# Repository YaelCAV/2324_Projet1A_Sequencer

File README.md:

# Projet-Sequenceur
> On souhaite créer un séquenceur musical qui émet des notes sur demande de l'utilisateur. Les notes doivent être variées et configurables, par exemple on souhaite pouvoir modifier leur hauteur, le nombre de répétitions par minute (bpm), et combiner les notes.
Pour cela on utilise sur conseil de l'un de nos professeurs un générateur de son programmable de Comodore 64 (dénomée MOS 6581) sortie en 1982.
La documentation de cette puce est facile d'accès et les possibilités qu'elle offrent satisfont nos exigences.
Comme mode de récupération du signal de sortie nous avons finalement choisi de proposer une sortie MIDI et Jack, il n'y a pas de haut-parleur intégré à notre séquenceur. L'alimentation de notre machine se fera par ailleurs via un port USB-C.

# Equipe
* Yael CAVAILLE-VOISIN
* Alexis NAUD
* Benoit LOMBARD
* Guilhem BOULARAN
* Louis GEORGE
> Rajouter vos github, linked in, etc...

# Journal de bord
> Déroulé séance par séance

## Séance 1 création du git, rédaction du cahier des charges et du plan, révision du cahier des charges.
## Séance 2 rendu du diagramme d'architecture, et des 3 bons de commande de composants, révision du cahier des charges et recherche des composants.
## Séance 3 CAO avec Kicad, changement de composants (boutons et LEDs RGB, hauts-parleurs, ampli audio).
## Séance 4 fin de conception du PCB et routage complet.
## Séance 5 récupération des composants et soudure, conception 3D, Architecture du code
## Séance 6 soudure + résolution des problèmes (d'empreinte des boutons-LED RG au lieu de RB via des PCB-adaptateurs imprimés à l'ENSEA), conception 3D
## Séance 7 soudure + résolution de problèmes, code, conception 3D
## Séance 8 soudure + résolution de problèmes, code, conception 3D
## Séance 9 code, présentation en séance, màj des livrables, résolution de problèmes liés au PCB et au processeur !
## Séance 10 code, création, compilation et vérification des livrables.

# Livrables
## PCB
> Présentation du schéma (grandes lignes) + PCB

## Code
> Architecture de votre code

## Rendu final
> Video ici de votre projet

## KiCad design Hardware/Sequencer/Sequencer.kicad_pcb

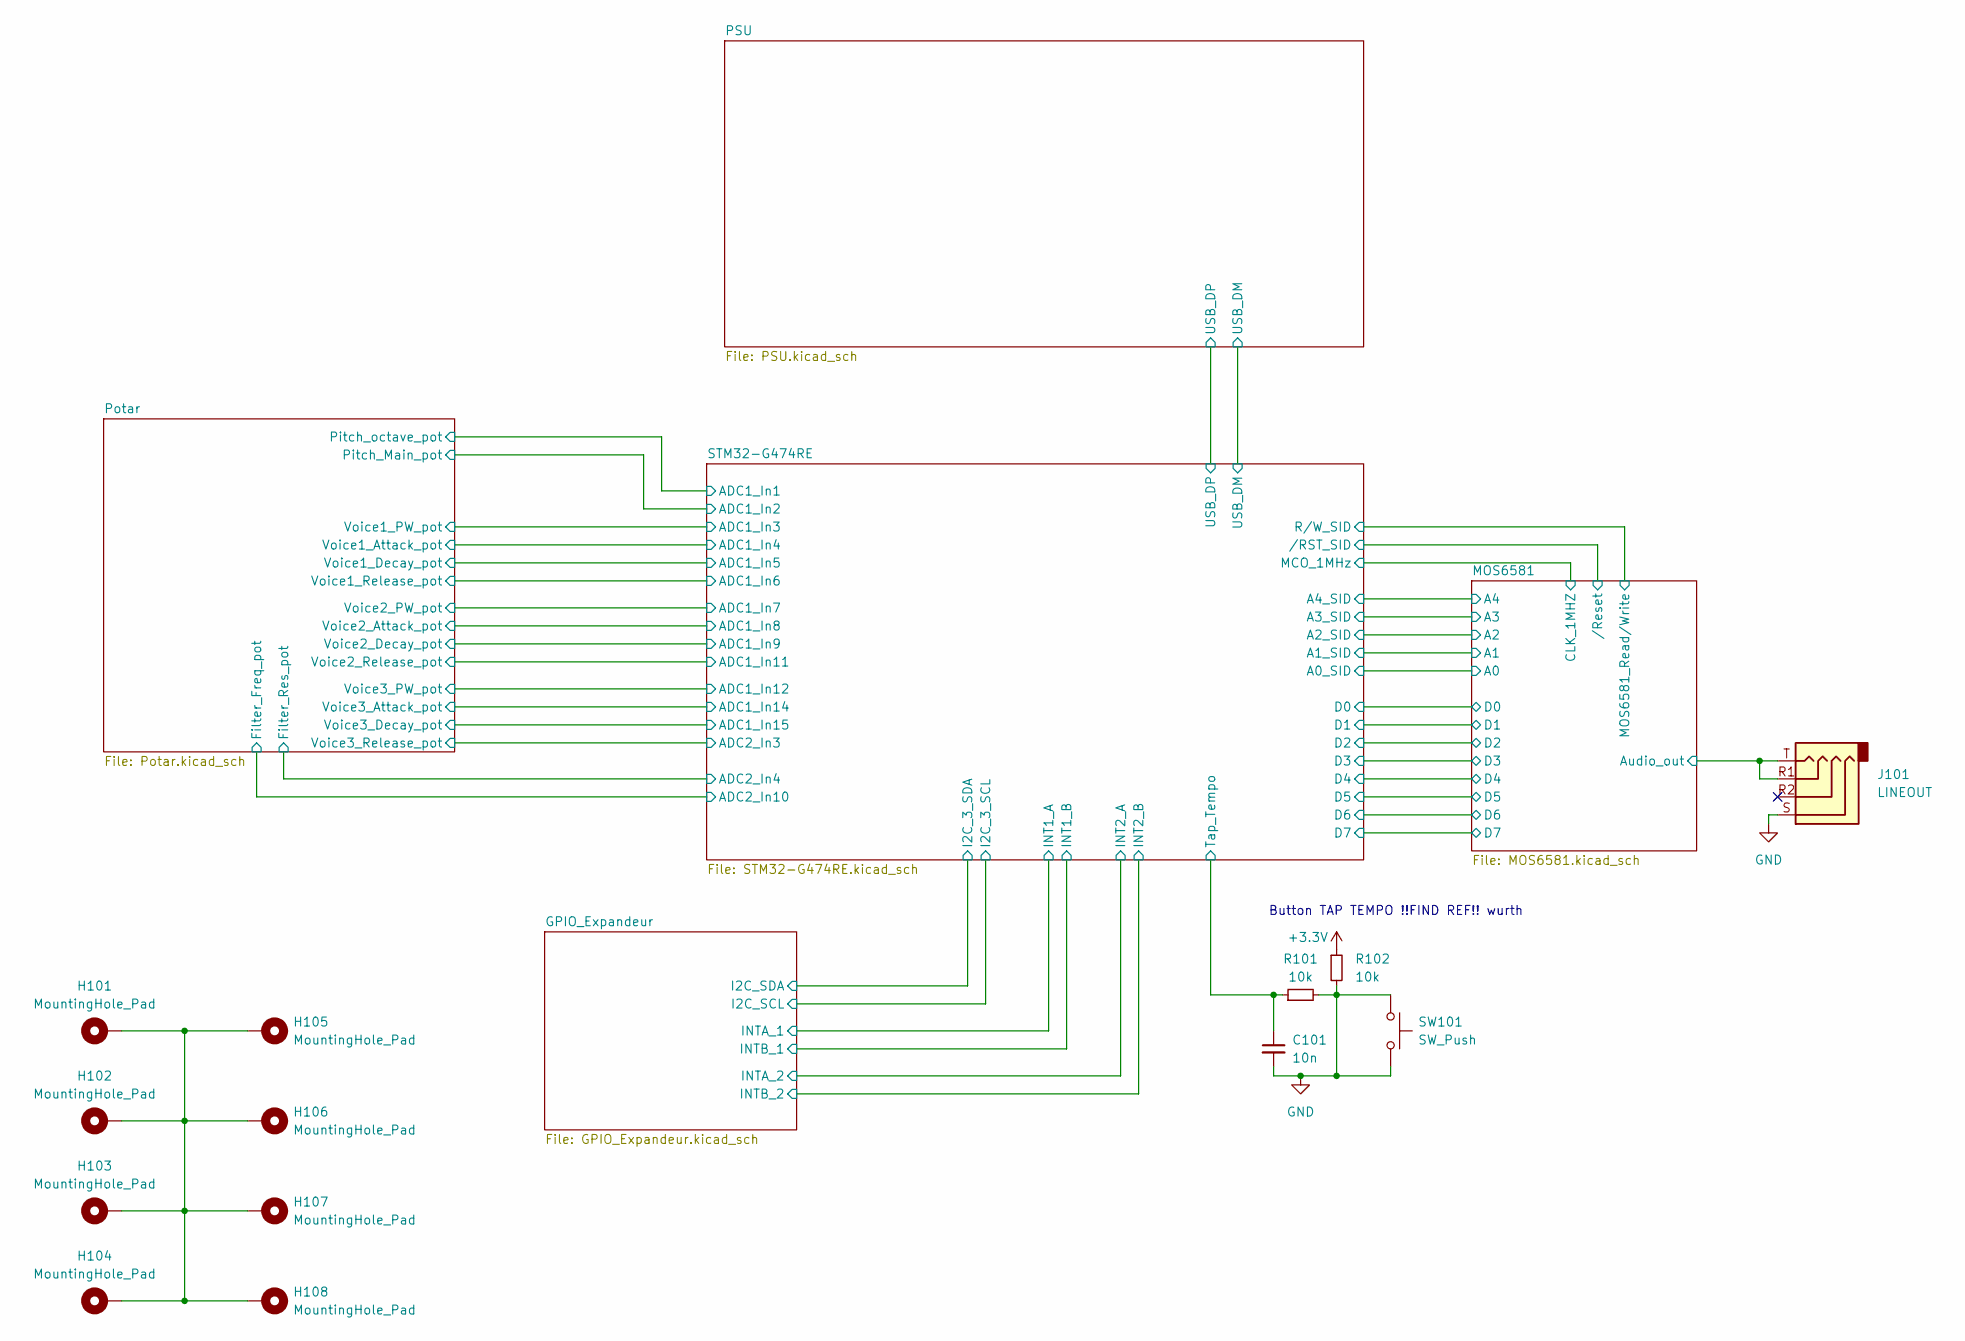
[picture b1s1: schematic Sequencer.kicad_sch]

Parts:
C101: 10n; C_0402_1005Metric
H101, H102, H103, H104, H105, H106, H107, H108: MountingHole_Pad; MountingHole_3.2mm_M3_Pad_Via
J101: LINEOUT; Jack_3.5mm_PJ320D_Horizontal; LCSC Part C431535
R101, R102: 10k; R_0402_1005Metric
SW101: SW_Push; SMT Push Button 12x12

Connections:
+3.3V: R102.1; also elsewhere on the board
/MOS6581/Audio_out: J101.R1, J101.T; also elsewhere on the board
/STM32-G474RE/Tap_Tempo: C101.1, R101.1; also elsewhere on the board
GND: C101.2, J101.S, R101.2, R102.2, SW101.1, SW101.2; also elsewhere on the board
unnamed: H101.1, H102.1, H103.1, H104.1, H105.1, H106.1, H107.1, H108.1

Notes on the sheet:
Button TAP TEMPO !!FIND REF!! wurth

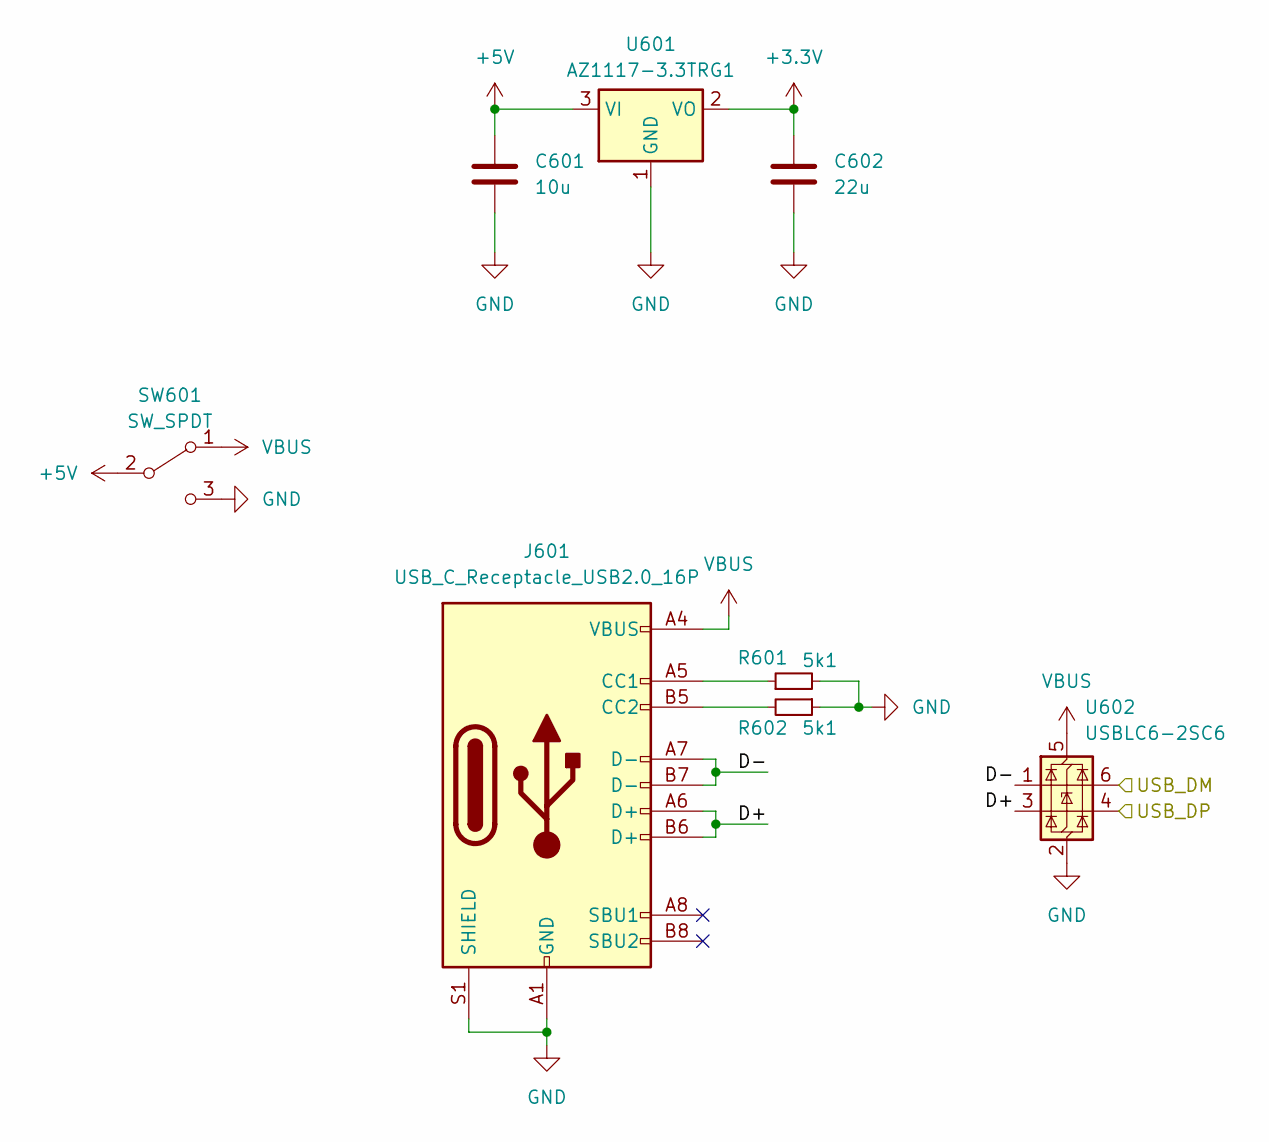
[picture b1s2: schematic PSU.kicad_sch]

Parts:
C601: 10u; C_0603_1608Metric
C602: 22u; C_0603_1608Metric
J601: USB_C_Receptacle_USB2.0_16P; USB_C_Receptacle_HRO_TYPE-C-31-M-12
R601, R602: 5k1; R_0402_1005Metric
SW601: SW_SPDT; 472121010111; MPN 472121010111
U601: AZ1117-3.3TRG1; SOT-223-3_TabPin2
U602: USBLC6-2SC6; SOT-23-6

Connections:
+3.3V: C602.1, U601.2 (VO); also elsewhere on the board
+5V: C601.1, SW601.2 (B), U601.3 (VI); also elsewhere on the board
/PSU/D+: J601.A6 (D+), J601.B6 (D+), U602.3 (I/O2)
/PSU/D-: J601.A7 (D-), J601.B7 (D-), U602.1 (I/O1)
/PSU/USB_DM: U602.6 (I/O1); also elsewhere on the board
/PSU/USB_DP: U602.4 (I/O2); also elsewhere on the board
GND: C601.2, C602.2, J601.A1 (GND), J601.A12 (GND), J601.B1 (GND), J601.B12 (GND), J601.S1 (SHIELD), R601.2, R602.1, SW601.3 (C), U601.1 (GND), U602.2 (GND); also elsewhere on the board
unnamed: J601.A5 (CC1), R601.1
unnamed: J601.B5 (CC2), R602.2
VBUS: J601.A4 (VBUS), J601.A9 (VBUS), J601.B4 (VBUS), J601.B9 (VBUS), SW601.1 (A), U602.5 (VBUS)

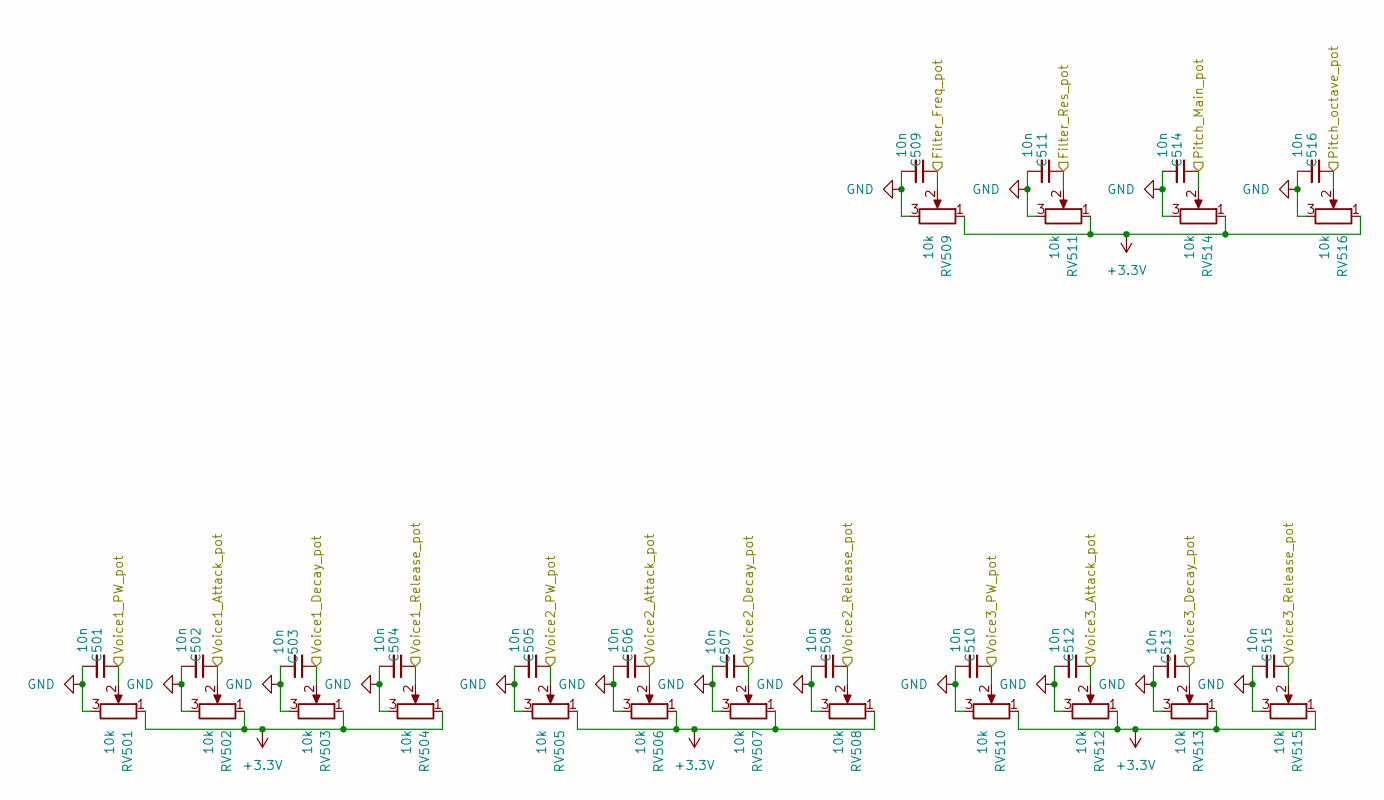
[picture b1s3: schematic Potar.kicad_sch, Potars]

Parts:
C501, C502, C503, C504, C505, C506, C507, C508, C509, C510, C511, C512, C513, C514, C515, C516: 10n; C_0402_1005Metric
RV501, RV502, RV503, RV504, RV505, RV506, RV507, RV508, RV509, RV510, RV511, RV512, RV513, RV515, RV516: 10k; Potentiometer_Alps_RK09K_Horizontal_CORRECTED
RV514: 10k; PTB6044-2010BPA103_BRN

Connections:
+3.3V: RV501.1, RV502.1, RV503.1, RV504.1, RV505.1, RV506.1, RV507.1, RV508.1, RV509.1, RV510.1, RV511.1, RV512.1, RV513.1, RV514.1, RV515.1, RV516.1; also elsewhere on the board
/Potar/Filter_Freq_pot: C509.1, RV509.2; also elsewhere on the board
/Potar/Filter_Res_pot: C511.1, RV511.2; also elsewhere on the board
/Potar/Pitch_Main_pot: C514.1, RV514.2; also elsewhere on the board
/Potar/Pitch_octave_pot: C516.1, RV516.2; also elsewhere on the board
/Potar/Voice1_Attack_pot: C502.1, RV502.2; also elsewhere on the board
/Potar/Voice1_Decay_pot: C503.1, RV503.2; also elsewhere on the board
/Potar/Voice1_PW_pot: C501.1, RV501.2; also elsewhere on the board
/Potar/Voice1_Release_pot: C504.1, RV504.2; also elsewhere on the board
/Potar/Voice2_Attack_pot: C506.1, RV506.2; also elsewhere on the board
/Potar/Voice2_Decay_pot: C507.1, RV507.2; also elsewhere on the board
/Potar/Voice2_PW_pot: C505.1, RV505.2; also elsewhere on the board
/Potar/Voice2_Release_pot: C508.1, RV508.2; also elsewhere on the board
/Potar/Voice3_Attack_pot: C512.1, RV512.2; also elsewhere on the board
/Potar/Voice3_Decay_pot: C513.1, RV513.2; also elsewhere on the board
/Potar/Voice3_PW_pot: C510.1, RV510.2; also elsewhere on the board
/Potar/Voice3_Release_pot: C515.1, RV515.2; also elsewhere on the board
GND: C501.2, C502.2, C503.2, C504.2, C505.2, C506.2, C507.2, C508.2, C509.2, C510.2, C511.2, C512.2, C513.2, C514.2, C515.2, C516.2, RV501.3, RV502.3, RV503.3, RV504.3, RV505.3, RV506.3, RV507.3, RV508.3, RV509.3, RV510.3, RV511.3, RV512.3, RV513.3, RV514.3, RV515.3, RV516.3; also elsewhere on the board

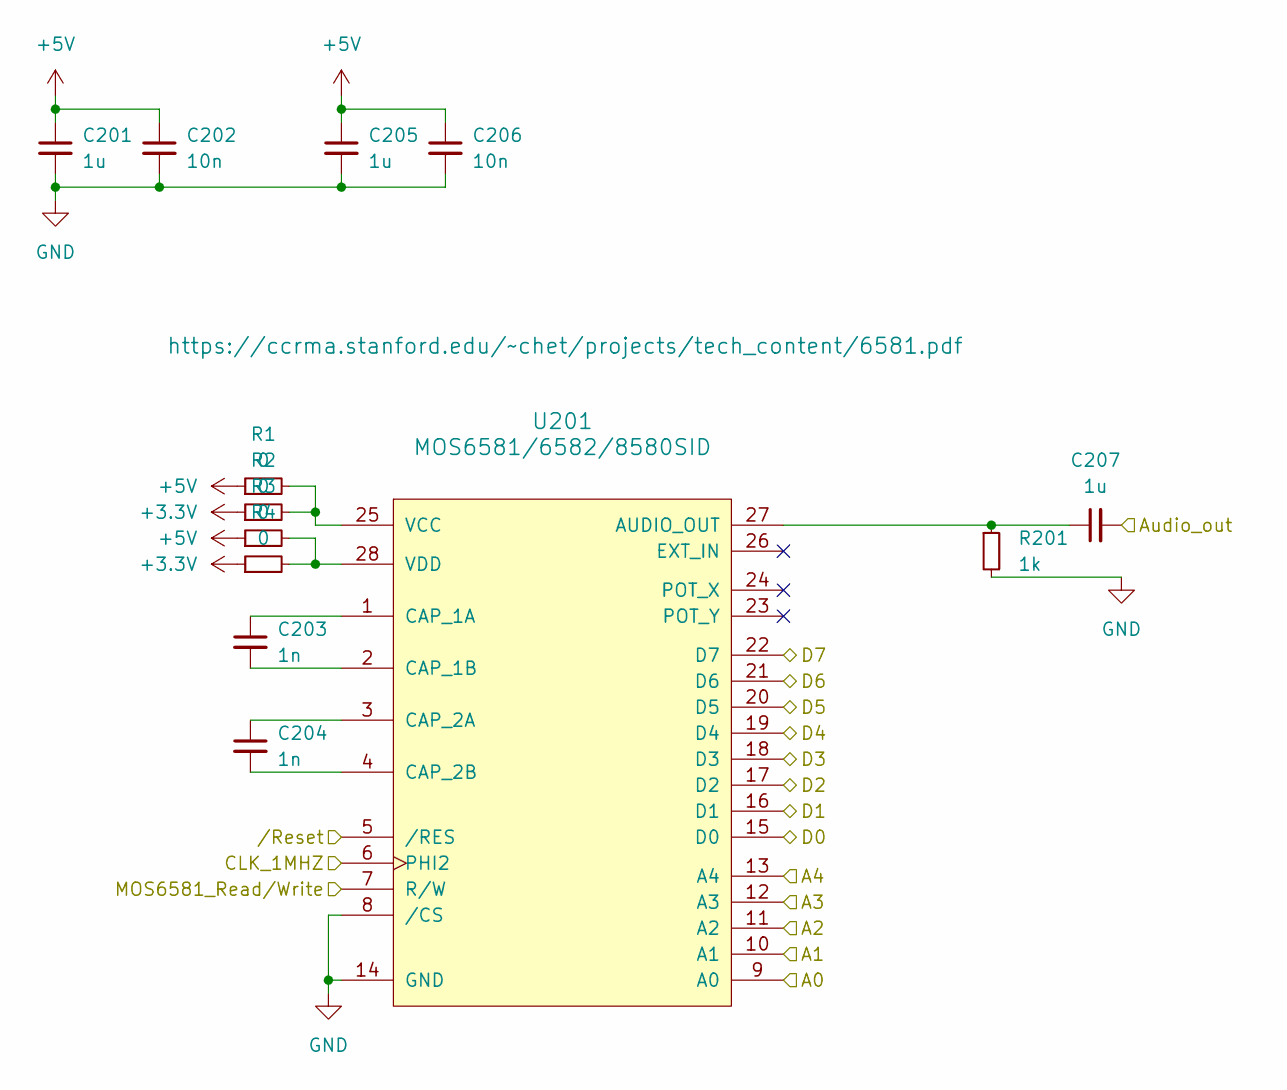
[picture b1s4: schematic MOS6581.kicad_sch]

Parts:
C201, C205, C207: 1u; C_0402_1005Metric
C202, C206: 10n; C_0402_1005Metric
C203, C204: 1n; C_0402_1005Metric
R1, R2, R3, R4: 0; R_0402_1005Metric
R201: 1k; R_0402_1005Metric
U201: MOS6581/6582/8580SID; DIP-28_W15.24mm_LongPads

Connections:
+3.3V: R2.1, R4.1; also elsewhere on the board
+5V: C201.1, C202.1, C205.1, C206.1, R1.1, R3.1; also elsewhere on the board
/MOS6581/A0: U201.9 (A0); also elsewhere on the board
/MOS6581/A1: U201.10 (A1); also elsewhere on the board
/MOS6581/A2: U201.11 (A2); also elsewhere on the board
/MOS6581/A3: U201.12 (A3); also elsewhere on the board
/MOS6581/A4: U201.13 (A4); also elsewhere on the board
/MOS6581/Audio_out: C207.2; also elsewhere on the board
/MOS6581/D0: U201.15 (D0); also elsewhere on the board
/MOS6581/D1: U201.16 (D1); also elsewhere on the board
/MOS6581/D2: U201.17 (D2); also elsewhere on the board
/MOS6581/D3: U201.18 (D3); also elsewhere on the board
/MOS6581/D4: U201.19 (D4); also elsewhere on the board
/MOS6581/D5: U201.20 (D5); also elsewhere on the board
/MOS6581/D6: U201.21 (D6); also elsewhere on the board
/MOS6581/D7: U201.22 (D7); also elsewhere on the board
/MOS6581/MOS6581_Read/Write: U201.7 (R/W); also elsewhere on the board
/MOS6581//Reset: U201.5 (/RES); also elsewhere on the board
/STM32-G474RE/NRST: U201.6 (PHI2); also elsewhere on the board
GND: C201.2, C202.2, C205.2, C206.2, R201.2, U201.8 (/CS), U201.14 (GND); also elsewhere on the board
unnamed: C207.1, R201.1, U201.27 (AUDIO_OUT)
unnamed: C203.1, U201.1 (CAP_1A)
unnamed: C203.2, U201.2 (CAP_1B)
unnamed: C204.1, U201.3 (CAP_2A)
unnamed: C204.2, U201.4 (CAP_2B)
unnamed: R1.2, R2.2, U201.25 (VCC)
unnamed: R3.2, R4.2, U201.28 (VDD)

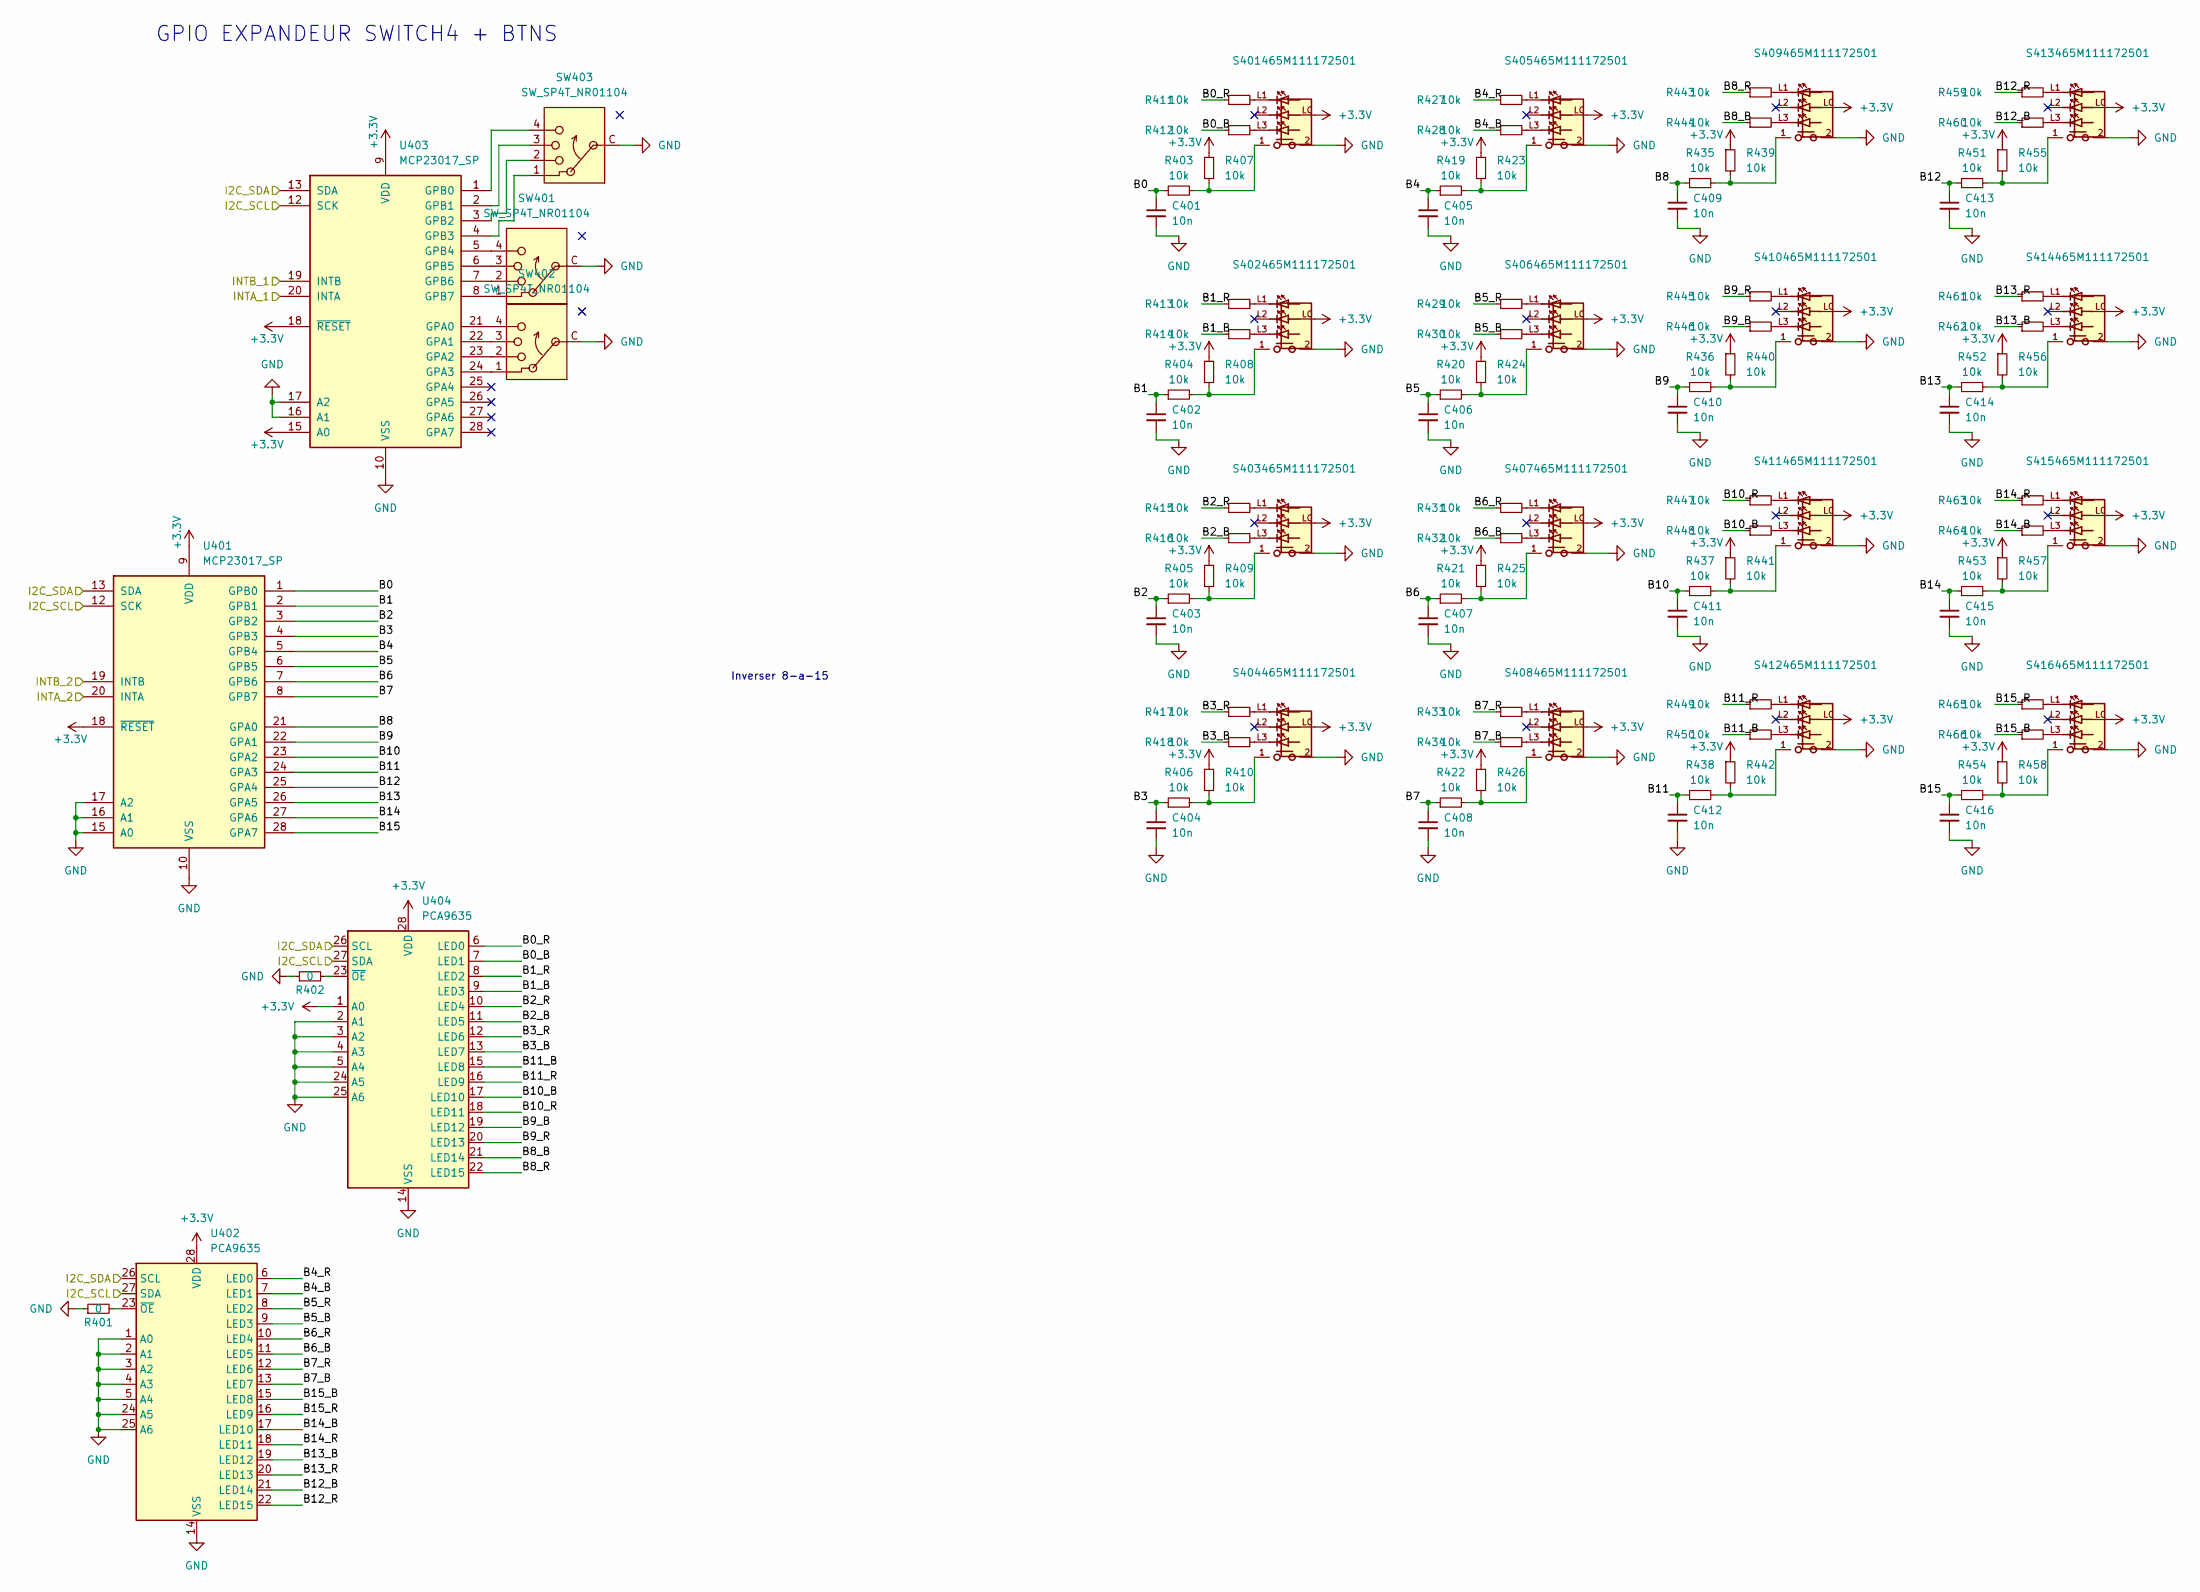
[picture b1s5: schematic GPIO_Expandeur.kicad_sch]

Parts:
C401, C402, C403, C404, C405, C406, C407, C408, C409, C410, C411, C412, C413, C414, C415, C416: 10n; C_0402_1005Metric
R401, R402: 0; R_0402_1005Metric
R403, R404, R405, R406, R407, R408, R409, R410, R411, R412, R413, R414, R415, R416, R417, R418, R419, R420, R421, R422, R423, R424, R425, R426, R427, R428, R429, R430, R431, R432, R433, R434, R435, R436, R437, R438, R439, R440, R441, R442, R443, R444, R445, R446, R447, R448, R449, R450, R451, R452, R453, R454, R455, R456, R457, R458, R459, R460, R461, R462, R463, R464, R465, R466: 10k; R_0402_1005Metric
S401, S402, S403, S404, S405, S406, S407, S408, S409, S410, S411, S412, S413, S414, S415, S416: 465M111172501; PART-NUMBER 465M111172501
SW401, SW402, SW403: SW_SP4T_NR01104; S-2050
U401, U403: MCP23017_SP; SOIC-28W_7.5x17.9mm_P1.27mm; MPN MCP23017-E/SO
U402, U404: PCA9635; TSSOP-28_4.4x9.7mm_P0.65mm

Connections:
+3.3V: R407.1, R408.1, R409.1, R410.1, R423.1, R424.1, R425.1, R426.1, R439.1, R440.1, R441.1, R442.1, R455.1, R456.1, R457.1, R458.1, S401.LC, S402.LC, S403.LC, S404.LC, S405.LC, S406.LC, S407.LC, S408.LC, S409.LC, S410.LC, S411.LC, S412.LC, S413.LC, S414.LC, S415.LC, S416.LC, U401.9 (VDD), U401.18 (~RESET), U402.28 (VDD), U403.9 (VDD), U403.15 (A0), U403.18 (~RESET), U404.1 (A0), U404.28 (VDD); also elsewhere on the board
/GPIO_Expandeur/B0: C401.1, R403.1, U401.1 (GPB0)
/GPIO_Expandeur/B0_B: R412.1, U404.7 (LED1)
/GPIO_Expandeur/B0_R: R411.1, U404.6 (LED0)
/GPIO_Expandeur/B1: C402.1, R404.1, U401.2 (GPB1)
/GPIO_Expandeur/B1_B: R414.1, U404.9 (LED3)
/GPIO_Expandeur/B1_R: R413.1, U404.8 (LED2)
/GPIO_Expandeur/B2: C403.1, R405.1, U401.3 (GPB2)
/GPIO_Expandeur/B2_B: R416.1, U404.11 (LED5)
/GPIO_Expandeur/B2_R: R415.1, U404.10 (LED4)
/GPIO_Expandeur/B3: C404.1, R406.1, U401.4 (GPB3)
/GPIO_Expandeur/B3_B: R418.1, U404.13 (LED7)
/GPIO_Expandeur/B3_R: R417.1, U404.12 (LED6)
/GPIO_Expandeur/B4: C405.1, R419.1, U401.5 (GPB4)
/GPIO_Expandeur/B4_B: R428.1, U402.7 (LED1)
/GPIO_Expandeur/B4_R: R427.1, U402.6 (LED0)
/GPIO_Expandeur/B5: C406.1, R420.1, U401.6 (GPB5)
/GPIO_Expandeur/B5_B: R430.1, U402.9 (LED3)
/GPIO_Expandeur/B5_R: R429.1, U402.8 (LED2)
/GPIO_Expandeur/B6: C407.1, R421.1, U401.7 (GPB6)
/GPIO_Expandeur/B6_B: R432.1, U402.11 (LED5)
/GPIO_Expandeur/B6_R: R431.1, U402.10 (LED4)
/GPIO_Expandeur/B7: C408.1, R422.1, U401.8 (GPB7)
/GPIO_Expandeur/B7_B: R434.1, U402.13 (LED7)
/GPIO_Expandeur/B7_R: R433.1, U402.12 (LED6)
/GPIO_Expandeur/B8: C409.1, R435.1, U401.21 (GPA0)
/GPIO_Expandeur/B8_B: R444.1, U404.21 (LED14)
/GPIO_Expandeur/B8_R: R443.1, U404.22 (LED15)
/GPIO_Expandeur/B9: C410.1, R436.1, U401.22 (GPA1)
/GPIO_Expandeur/B9_B: R446.1, U404.19 (LED12)
/GPIO_Expandeur/B9_R: R445.1, U404.20 (LED13)
/GPIO_Expandeur/B10: C411.1, R437.1, U401.23 (GPA2)
/GPIO_Expandeur/B10_B: R448.1, U404.17 (LED10)
/GPIO_Expandeur/B10_R: R447.1, U404.18 (LED11)
/GPIO_Expandeur/B11: C412.1, R438.1, U401.24 (GPA3)
/GPIO_Expandeur/B11_B: R450.1, U404.15 (LED8)
/GPIO_Expandeur/B11_R: R449.1, U404.16 (LED9)
/GPIO_Expandeur/B12: C413.1, R451.1, U401.25 (GPA4)
/GPIO_Expandeur/B12_B: R460.1, U402.21 (LED14)
/GPIO_Expandeur/B12_R: R459.1, U402.22 (LED15)
/GPIO_Expandeur/B13: C414.1, R452.1, U401.26 (GPA5)
/GPIO_Expandeur/B13_B: R462.1, U402.19 (LED12)
/GPIO_Expandeur/B13_R: R461.1, U402.20 (LED13)
/GPIO_Expandeur/B14: C415.1, R453.1, U401.27 (GPA6)
/GPIO_Expandeur/B14_B: R464.1, U402.17 (LED10)
/GPIO_Expandeur/B14_R: R463.1, U402.18 (LED11)
/GPIO_Expandeur/B15: C416.1, R454.1, U401.28 (GPA7)
/GPIO_Expandeur/B15_B: R466.1, U402.15 (LED8)
/GPIO_Expandeur/B15_R: R465.1, U402.16 (LED9)
/GPIO_Expandeur/I2C_SCL: U401.12 (SCK), U402.27 (SDA), U403.12 (SCK), U404.27 (SDA); also elsewhere on the board
/GPIO_Expandeur/I2C_SDA: U401.13 (SDA), U402.26 (SCL), U403.13 (SDA), U404.26 (SCL); also elsewhere on the board
/GPIO_Expandeur/INTA_1: U403.20 (INTA); also elsewhere on the board
/GPIO_Expandeur/INTA_2: U401.20 (INTA); also elsewhere on the board
/GPIO_Expandeur/INTB_1: U403.19 (INTB); also elsewhere on the board
/GPIO_Expandeur/INTB_2: U401.19 (INTB); also elsewhere on the board
GND: C401.2, C402.2, C403.2, C404.2, C405.2, C406.2, C407.2, C408.2, C409.2, C410.2, C411.2, C412.2, C413.2, C414.2, C415.2, C416.2, R401.1, R402.1, S401.2, S402.2, S403.2, S404.2, S405.2, S406.2, S407.2, S408.2, S409.2, S410.2, S411.2, S412.2, S413.2, S414.2, S415.2, S416.2, SW401.C (Common), SW402.C (Common), SW403.C (Common), U401.10 (VSS), U401.15 (A0), U401.16 (A1), U401.17 (A2), U402.1 (A0), U402.2 (A1), U402.3 (A2), U402.4 (A3), U402.5 (A4), U402.14 (VSS), U402.24 (A5), U402.25 (A6), U403.10 (VSS), U403.16 (A1), U403.17 (A2), U404.2 (A1), U404.3 (A2), U404.4 (A3), U404.5 (A4), U404.14 (VSS), U404.24 (A5), U404.25 (A6); also elsewhere on the board
unnamed: R403.2, R407.2, S401.1
unnamed: R404.2, R408.2, S402.1
unnamed: R405.2, R409.2, S403.1
unnamed: R406.2, R410.2, S404.1
unnamed: R411.2, S401.L1
unnamed: R412.2, S401.L3
unnamed: R413.2, S402.L1
unnamed: R414.2, S402.L3
unnamed: R415.2, S403.L1
unnamed: R416.2, S403.L3
unnamed: R417.2, S404.L1
unnamed: R418.2, S404.L3
unnamed: R419.2, R423.2, S405.1
unnamed: R420.2, R424.2, S406.1
unnamed: R421.2, R425.2, S407.1
unnamed: R422.2, R426.2, S408.1
unnamed: R427.2, S405.L1
unnamed: R428.2, S405.L3
unnamed: R429.2, S406.L1
unnamed: R430.2, S406.L3
unnamed: R431.2, S407.L1
unnamed: R432.2, S407.L3
unnamed: R433.2, S408.L1
unnamed: R434.2, S408.L3
unnamed: R435.2, R439.2, S409.1
unnamed: R436.2, R440.2, S410.1
unnamed: R437.2, R441.2, S411.1
unnamed: R438.2, R442.2, S412.1
unnamed: R443.2, S409.L1
unnamed: R444.2, S409.L3
unnamed: R445.2, S410.L1
unnamed: R446.2, S410.L3
unnamed: R447.2, S411.L1
unnamed: R448.2, S411.L3
unnamed: R449.2, S412.L1
unnamed: R450.2, S412.L3
unnamed: R451.2, R455.2, S413.1
unnamed: R452.2, R456.2, S414.1
unnamed: R453.2, R457.2, S415.1
unnamed: R454.2, R458.2, S416.1
unnamed: R459.2, S413.L1
unnamed: R460.2, S413.L3
unnamed: R461.2, S414.L1
unnamed: R462.2, S414.L3
unnamed: R463.2, S415.L1
unnamed: R464.2, S415.L3
unnamed: R465.2, S416.L1
unnamed: R466.2, S416.L3
unnamed: R401.2, U402.23 (~OE)
unnamed: SW402.4, U403.21 (GPA0)
unnamed: SW402.3, U403.22 (GPA1)
unnamed: SW402.2, U403.23 (GPA2)
unnamed: SW402.1, U403.24 (GPA3)
unnamed: SW403.4, U403.1 (GPB0)
unnamed: SW403.3, U403.2 (GPB1)
unnamed: SW403.2, U403.3 (GPB2)
unnamed: SW403.1, U403.4 (GPB3)
unnamed: SW401.4, U403.5 (GPB4)
unnamed: SW401.3, U403.6 (GPB5)
unnamed: SW401.2, U403.7 (GPB6)
unnamed: SW401.1, U403.8 (GPB7)
unnamed: R402.2, U404.23 (~OE)

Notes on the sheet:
GPIO EXPANDEUR SWITCH4 + BTNS
Inverser 8-a-15

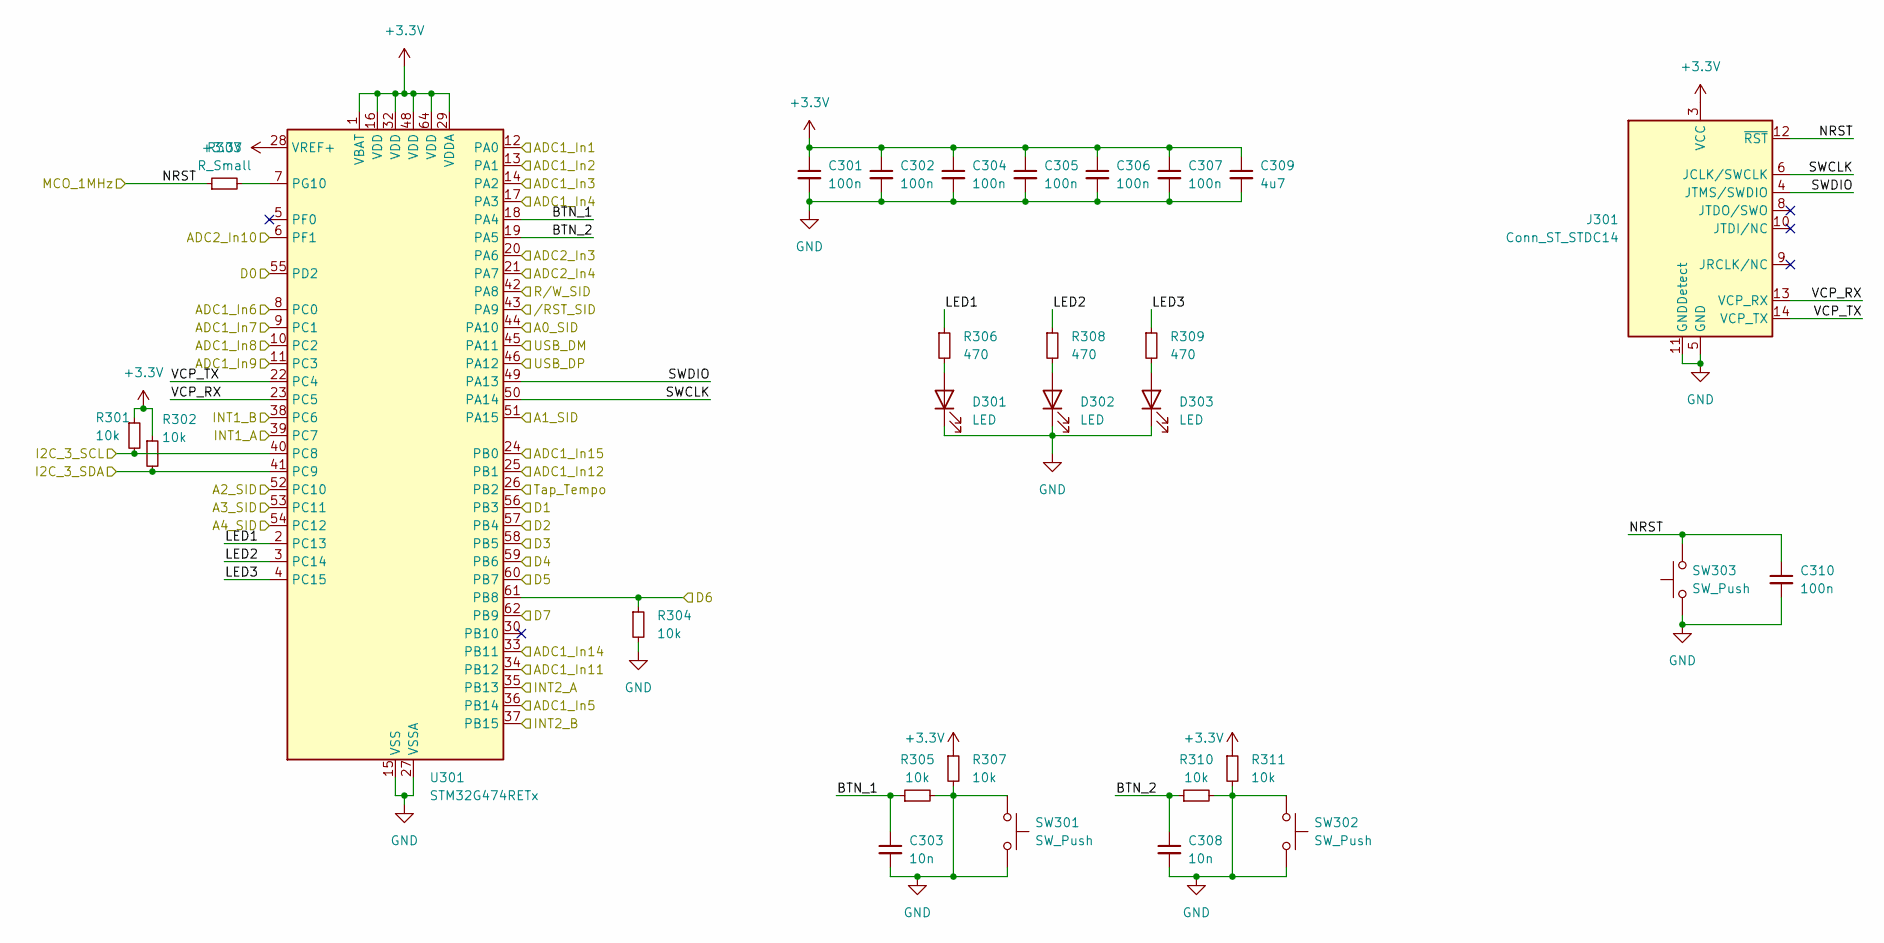
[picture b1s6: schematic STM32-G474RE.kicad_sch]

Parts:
C301, C302, C304, C305, C306, C307, C310: 100n; C_0402_1005Metric
C303, C308: 10n; C_0402_1005Metric
C309: 4u7; C_0402_1005Metric
D301, D302, D303: LED; LED_0603_1608Metric
J301: Conn_ST_STDC14; PinHeader_2x07_P1.27mm_Vertical_SMD
R301, R302, R304, R305, R307, R310, R311: 10k; R_0402_1005Metric
R303: R_Small; R_0402_1005Metric
R306, R308, R309: 470; R_0402_1005Metric
SW301, SW302, SW303: SW_Push; SW_Push_1P1T_NO_6x6mm_H9.5mm
U301: STM32G474RETx; LQFP-64_10x10mm_P0.5mm

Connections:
+3.3V: C301.1, C302.1, C304.1, C305.1, C306.1, C307.1, C309.1, J301.3 (VCC), R301.1, R302.1, R307.1, R311.1, U301.1 (VBAT), U301.16 (VDD), U301.28 (VREF+), U301.29 (VDDA), U301.32 (VDD), U301.48 (VDD), U301.64 (VDD); also elsewhere on the board
/GPIO_Expandeur/I2C_SCL: R301.2, U301.40 (PC8); also elsewhere on the board
/GPIO_Expandeur/I2C_SDA: R302.2, U301.41 (PC9); also elsewhere on the board
/GPIO_Expandeur/INTA_1: U301.39 (PC7); also elsewhere on the board
/GPIO_Expandeur/INTA_2: U301.35 (PB13); also elsewhere on the board
/GPIO_Expandeur/INTB_1: U301.38 (PC6); also elsewhere on the board
/GPIO_Expandeur/INTB_2: U301.37 (PB15); also elsewhere on the board
/MOS6581/A0: U301.44 (PA10); also elsewhere on the board
/MOS6581/A1: U301.51 (PA15); also elsewhere on the board
/MOS6581/A2: U301.52 (PC10); also elsewhere on the board
/MOS6581/A3: U301.53 (PC11); also elsewhere on the board
/MOS6581/A4: U301.54 (PC12); also elsewhere on the board
/MOS6581/D0: U301.55 (PD2); also elsewhere on the board
/MOS6581/D1: U301.56 (PB3); also elsewhere on the board
/MOS6581/D2: U301.57 (PB4); also elsewhere on the board
/MOS6581/D3: U301.58 (PB5); also elsewhere on the board
/MOS6581/D4: U301.59 (PB6); also elsewhere on the board
/MOS6581/D5: U301.60 (PB7); also elsewhere on the board
/MOS6581/D6: R304.1, U301.61 (PB8); also elsewhere on the board
/MOS6581/D7: U301.62 (PB9); also elsewhere on the board
/MOS6581/MOS6581_Read/Write: U301.42 (PA8); also elsewhere on the board
/MOS6581//Reset: U301.43 (PA9); also elsewhere on the board
/PSU/USB_DM: U301.45 (PA11); also elsewhere on the board
/PSU/USB_DP: U301.46 (PA12); also elsewhere on the board
/Potar/Filter_Freq_pot: U301.6 (PF1); also elsewhere on the board
/Potar/Filter_Res_pot: U301.21 (PA7); also elsewhere on the board
/Potar/Pitch_Main_pot: U301.13 (PA1); also elsewhere on the board
/Potar/Pitch_octave_pot: U301.12 (PA0); also elsewhere on the board
/Potar/Voice1_Attack_pot: U301.17 (PA3); also elsewhere on the board
/Potar/Voice1_Decay_pot: U301.36 (PB14); also elsewhere on the board
/Potar/Voice1_PW_pot: U301.14 (PA2); also elsewhere on the board
/Potar/Voice1_Release_pot: U301.8 (PC0); also elsewhere on the board
/Potar/Voice2_Attack_pot: U301.10 (PC2); also elsewhere on the board
/Potar/Voice2_Decay_pot: U301.11 (PC3); also elsewhere on the board
/Potar/Voice2_PW_pot: U301.9 (PC1); also elsewhere on the board
/Potar/Voice2_Release_pot: U301.34 (PB12); also elsewhere on the board
/Potar/Voice3_Attack_pot: U301.33 (PB11); also elsewhere on the board
/Potar/Voice3_Decay_pot: U301.24 (PB0); also elsewhere on the board
/Potar/Voice3_PW_pot: U301.25 (PB1); also elsewhere on the board
/Potar/Voice3_Release_pot: U301.20 (PA6); also elsewhere on the board
/STM32-G474RE/BTN_1: C303.1, R305.1, U301.18 (PA4)
/STM32-G474RE/BTN_2: C308.1, R310.1, U301.19 (PA5)
/STM32-G474RE/LED1: R306.1, U301.2 (PC13)
/STM32-G474RE/LED2: R308.1, U301.3 (PC14)
/STM32-G474RE/LED3: R309.1, U301.4 (PC15)
/STM32-G474RE/NRST: C310.1, J301.12 (~RST), R303.1, SW303.2; also elsewhere on the board
/STM32-G474RE/SWCLK: J301.6 (JCLK/SWCLK), U301.50 (PA14)
/STM32-G474RE/SWDIO: J301.4 (JTMS/SWDIO), U301.49 (PA13)
/STM32-G474RE/Tap_Tempo: U301.26 (PB2); also elsewhere on the board
/STM32-G474RE/VCP_RX: J301.13 (VCP_RX), U301.23 (PC5)
/STM32-G474RE/VCP_TX: J301.14 (VCP_TX), U301.22 (PC4)
GND: C301.2, C302.2, C303.2, C304.2, C305.2, C306.2, C307.2, C308.2, C309.2, C310.2, D301.1 (K), D302.1 (K), D303.1 (K), J301.5 (GND), J301.7 (GND), J301.11 (GNDDetect), R304.2, R305.2, R307.2, R310.2, R311.2, SW301.1, SW301.2, SW302.1, SW302.2, SW303.1, U301.15 (VSS), U301.27 (VSSA), U301.31 (VSS), U301.47 (VSS), U301.63 (VSS); also elsewhere on the board
unnamed: D301.2 (A), R306.2
unnamed: D302.2 (A), R308.2
unnamed: D303.2 (A), R309.2
unnamed: R303.2, U301.7 (PG10)
